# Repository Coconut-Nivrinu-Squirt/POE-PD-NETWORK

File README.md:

# Power Over Ethernet network adapter with type C power Delivery Ciurcit

## Legal and Licensing Architecture

This is a hardware-primary open-source project utilizing a strict dual-license architecture to protect both the physical board design and the firmware blobs.

*   **Hardware Design:** All physical design files, CAD models, schematics, and PCB layouts are licensed under the **CERN Open Hardware Licence Version 2 - Strongly Reciprocal (CERN-OHL-S v2)**.
*   **Firmware & Software:** All source code, firmware, and software required to operate this hardware (located in the `/firmware` directory) are licensed under the **European Union Public License v1.2 (EUPL-1.2)**.
*   **Provenance:** The Open Source Hardware (OSHW) gear logo and pending OSHWA UID (`OSHWA UID: [PENDING]`) act as physical marks of original provenance. **Use of theese marks in your product constitutes a commitment to open sourcing your derivative work!!!** 

See the root `LICENSE` file and the `LICENSES/` directory for full unmodified legal texts.

# Project Source credits
Some footprints and symbols in this project are sourced under fair use terms from [Ultra Librarian](https://www.ultralibrarian.com/)

*this project is a work in progress. Things may update randomly!*
### This is an Open source project intended to let you build your own combination Power delivery Source With a network adapter.
|Supported power source type | Voltages supplied | Source |
| ------------ | -------------- | -------------- |
| External Power Supply | 5VDC, 3.3VDC, 25VDC | 5 pin Screw lock plug of choice |
| Internal Power Supply | 5VDC, 3.3VDC, 25VDC | POE power source curcitry |
| USB OTG Power Supply | 5VDC, 3.3VDC | Vbus - Sourced from attached device |

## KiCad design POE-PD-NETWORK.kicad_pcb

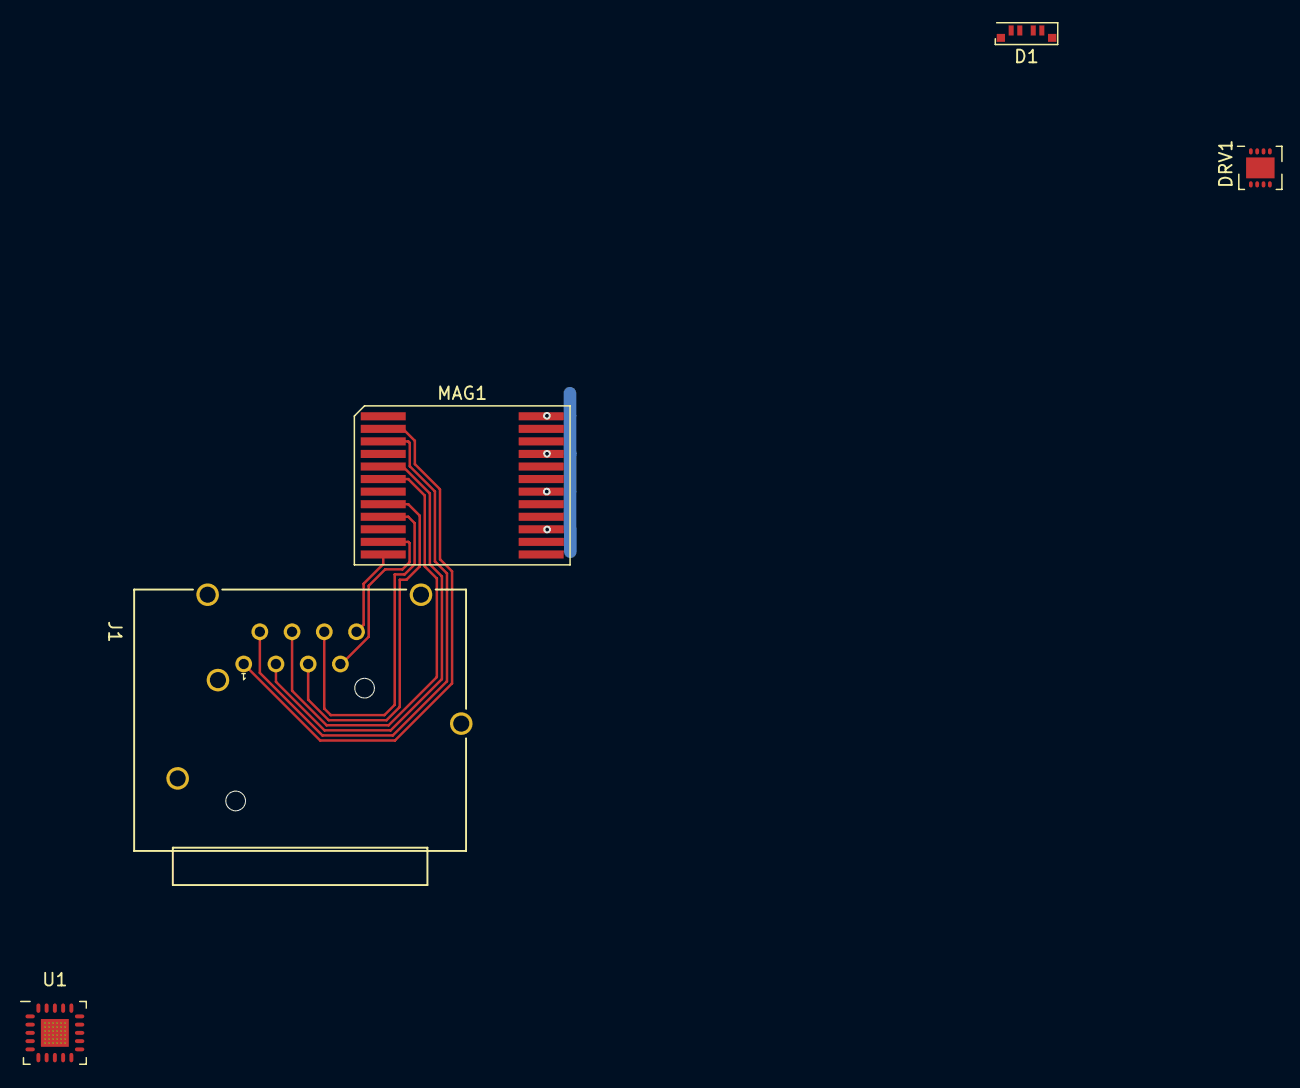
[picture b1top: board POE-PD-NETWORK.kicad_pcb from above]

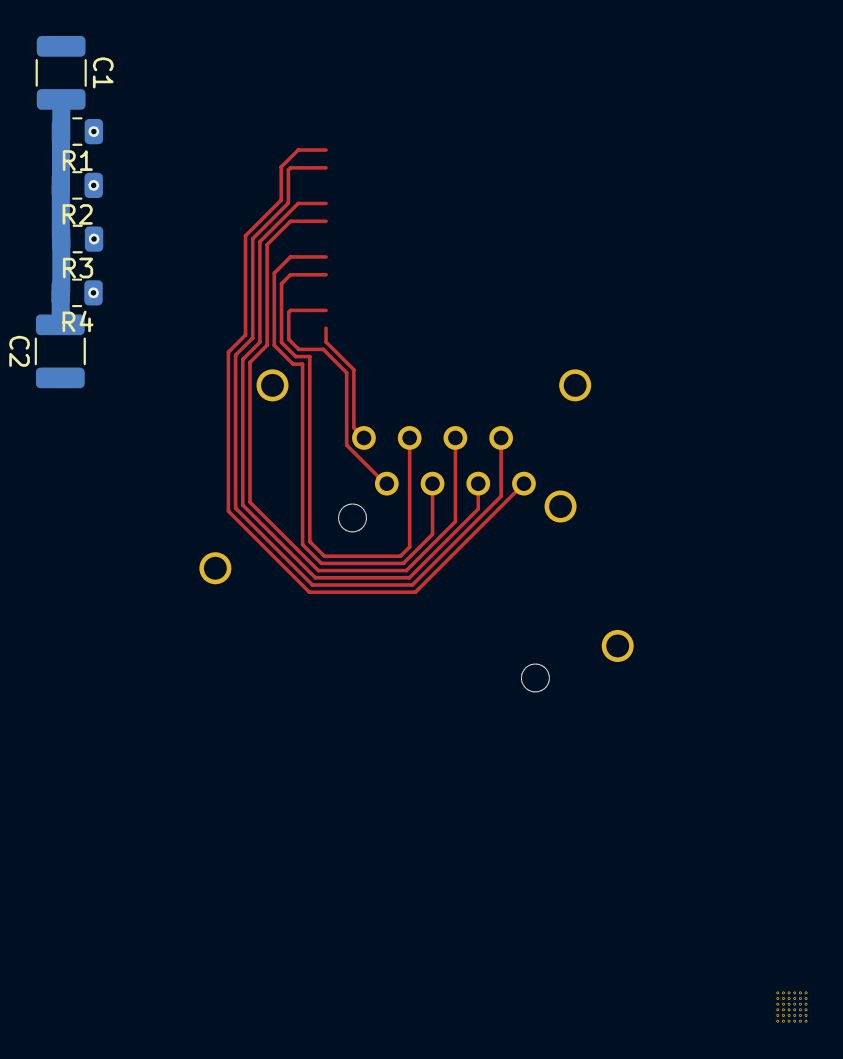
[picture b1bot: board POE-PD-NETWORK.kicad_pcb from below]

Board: 8 copper layers, 11 parts (6 on the bottom side), 19 nets.

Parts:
C1, C2: C; C_1210_3225Metric
D1: QLS6B-FKW; LED_Cree-PLCC6_4.7x1.5mm
DRV1: PCA9632-HVSON
J1: 8P8C-NE8FBH-C5-S; CONN_NE8FBH-S_NTK
MAG1: HDX8005NL
R1, R2, R3, R4: R; R_0805_2012Metric
U1: TI TPS2373-4RGWR

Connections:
+3.3V: D1.1 (AB), D1.3 (AR), D1.5 (AG)
CHS_GND: J1.G, J1.S
GND: C1.1, C2.1, DRV1.5 (VSS), DRV1.9 (EP)
unnamed: C1.2, C2.2, R1.2, R2.2, R3.2, R4.2
unnamed: D1.2 (KB), DRV1.3 (LED2)
unnamed: D1.6 (KR), DRV1.1 (LED0)
unnamed: D1.4 (KR), DRV1.2 (LED1)
unnamed: MAG1.24 (MCT1), R1.1
unnamed: MAG1.21 (MCT2), R2.1
unnamed: MAG1.18 (MCT3), R3.1
unnamed: MAG1.15 (MCT4), R4.1
unnamed: J1.1, MAG1.2 (TD1+)
unnamed: J1.2, MAG1.3 (TD1-)
unnamed: J1.3, MAG1.5 (TD2+)
unnamed: J1.4, MAG1.6 (TD2-)
unnamed: J1.5, MAG1.8 (TD3+)
unnamed: J1.6, MAG1.9 (TD3-)
unnamed: J1.7, MAG1.11 (TD4+)
unnamed: J1.8, MAG1.12 (TD4-)

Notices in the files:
POE-PD-NETWORK.kicad_pcb:
Copyright © 2026 Coconut Nivrinu Squirt
Licensed under CERN-OHL-S v2
README.md:
Hardware License
